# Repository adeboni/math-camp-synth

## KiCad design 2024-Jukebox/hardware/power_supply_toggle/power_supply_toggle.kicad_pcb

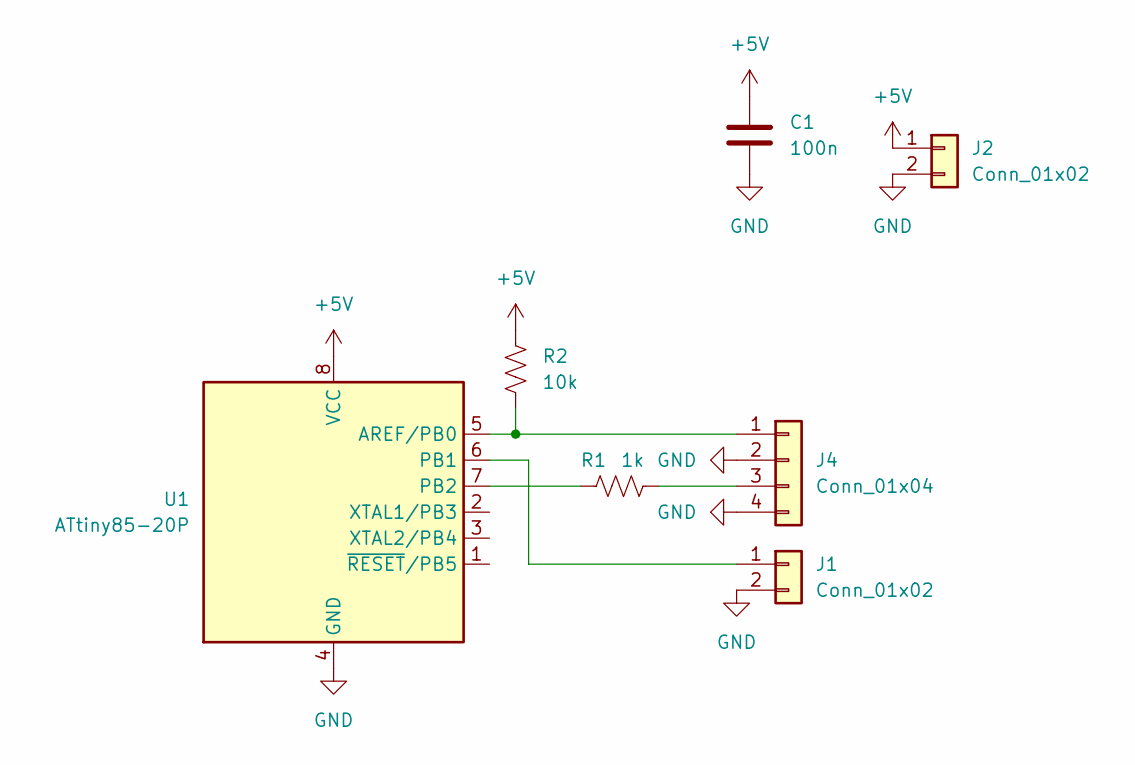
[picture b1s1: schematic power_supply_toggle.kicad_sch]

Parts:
C1: 100n; C_0603_1608Metric
J1, J2: Conn_01x02; PinHeader_1x02_P2.54mm_Vertical
J4: Conn_01x04; JST_XH_B4B-XH-A_1x04_P2.50mm_Vertical
R1: 1k; R_0603_1608Metric
R2: 10k; R_0603_1608Metric
U1: ATtiny85-20P; DIP-8_W7.62mm

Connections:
+5V: C1.1, J2.1, R2.1, U1.8 (VCC)
GND: C1.2, J1.2, J2.2, J4.2, J4.4, U1.4 (GND)
unnamed: J1.1, U1.6 (PB1)
unnamed: J4.1, R2.2, U1.5 (AREF/PB0)
unnamed: J4.3, R1.2
unnamed: R1.1, U1.7 (PB2)

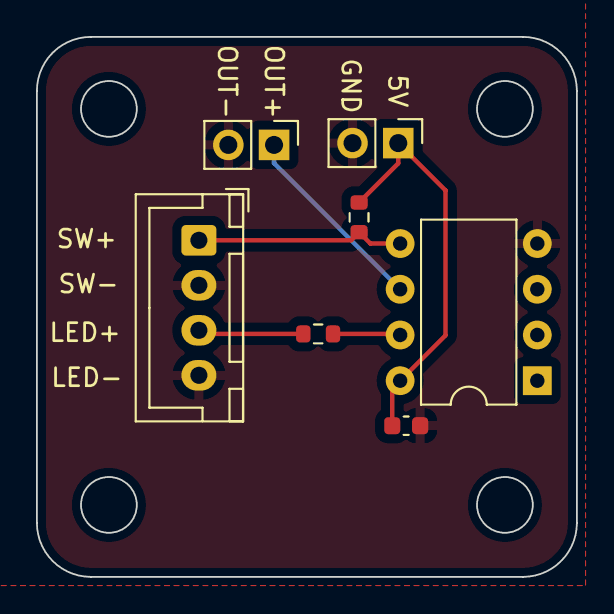
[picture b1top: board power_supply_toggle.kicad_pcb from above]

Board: 2 copper layers, 30.0 x 30.0 mm, 7 parts (0 on the bottom side), 6 nets.

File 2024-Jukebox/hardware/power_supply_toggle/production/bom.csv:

Designator,Footprint,Quantity,Value,LCSC Part #
C1,0603,1,100n,
"J1, J2",PinHeader_1x02_P2.54mm_Vertical,2,Conn_01x02,
J4,JST_XH_B4B-XH-A_1x04_P2.50mm_Vertical,1,Conn_01x04,
R1,0603,1,1k,
R2,0603,1,10k,
U1,DIP-8_W7.62mm,1,ATtiny85-20P,

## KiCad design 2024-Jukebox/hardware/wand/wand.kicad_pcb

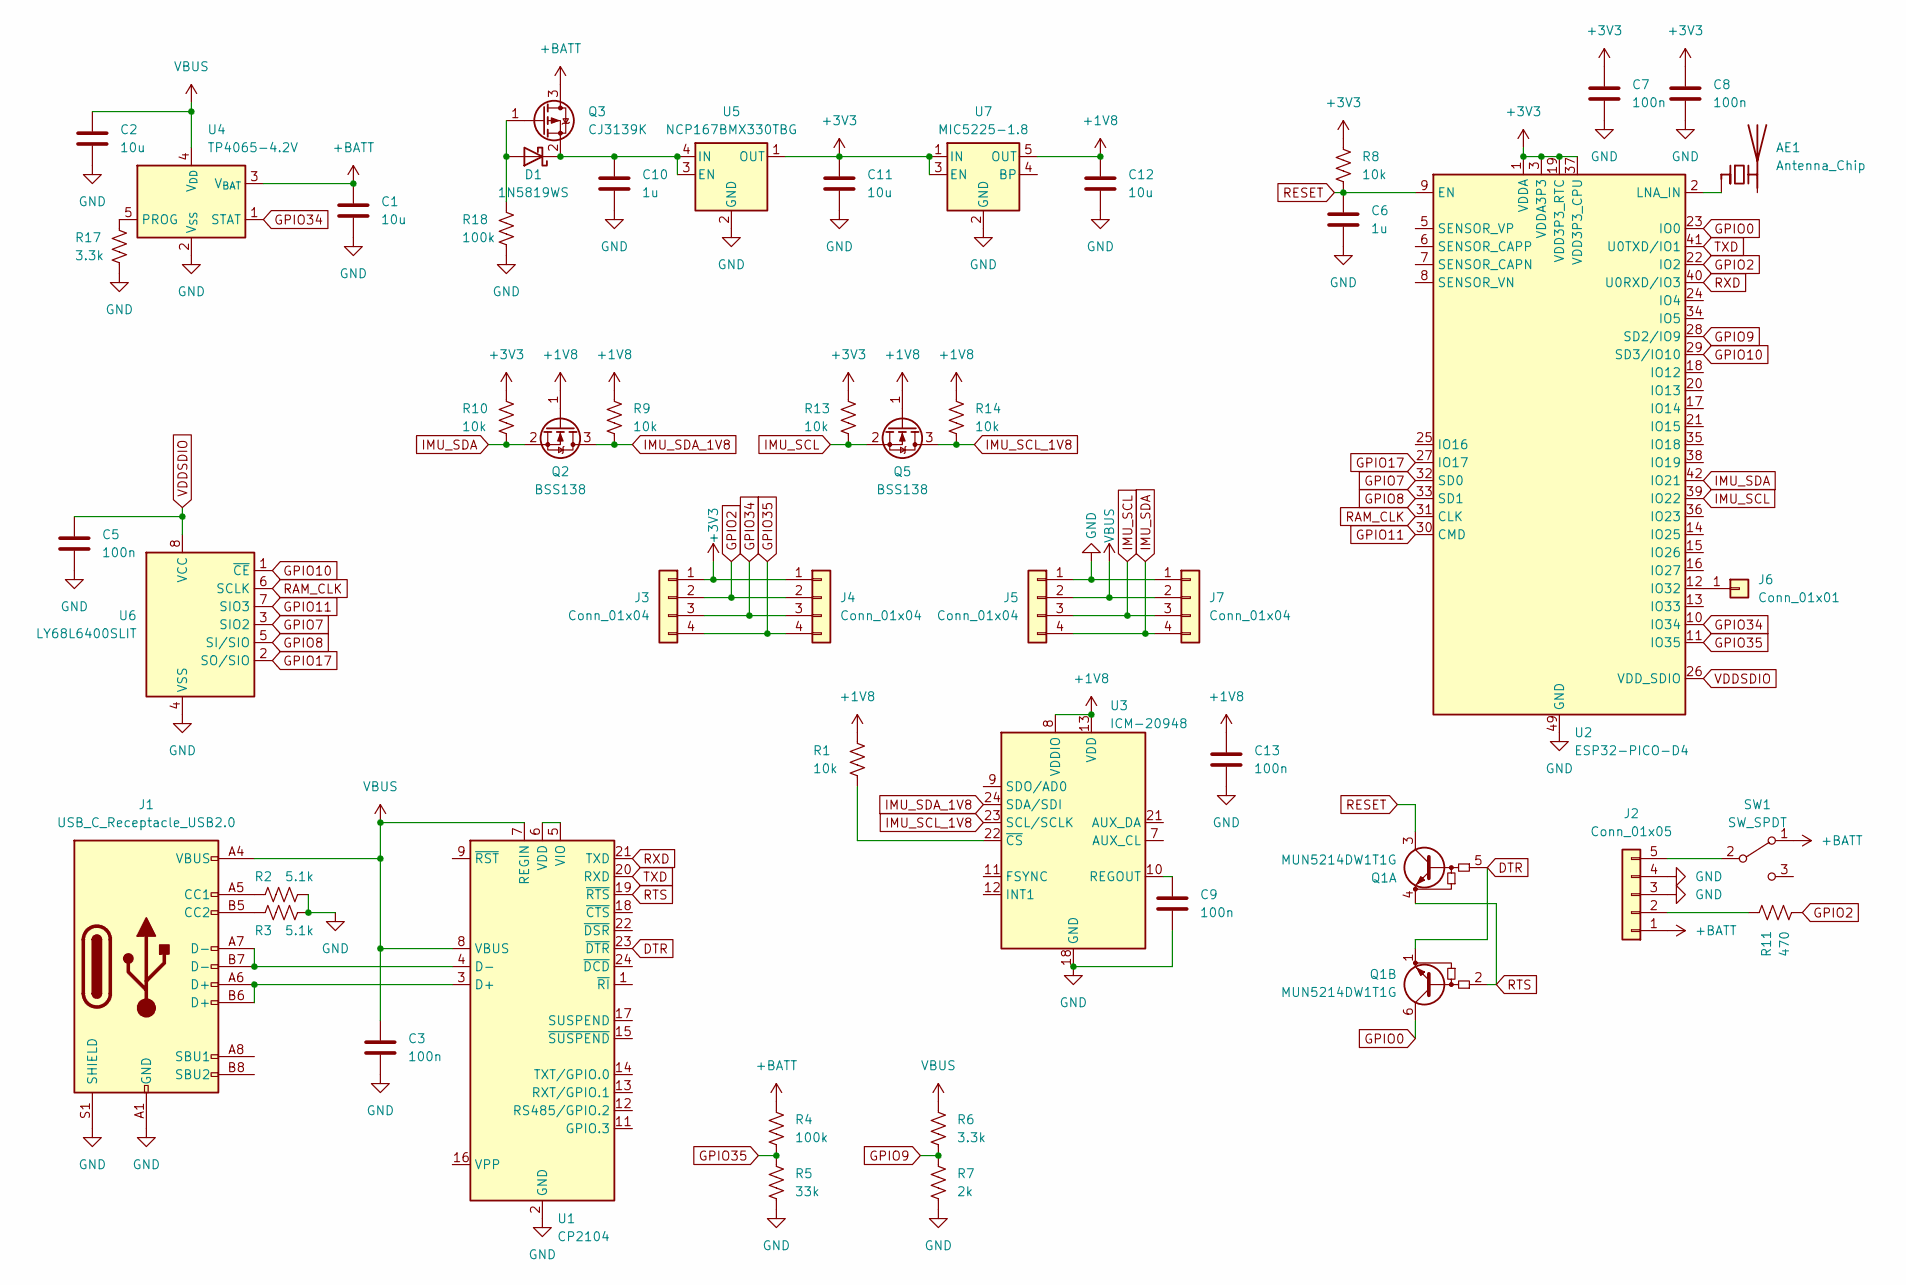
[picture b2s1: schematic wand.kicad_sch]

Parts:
AE1: Antenna_Chip; C_1206_3216Metric
C1, C2, C11, C12: 10u; C_0402_1005Metric
C3, C5, C7, C8, C9, C13: 100n; C_0402_1005Metric
C6, C10: 1u; C_0402_1005Metric
D1: 1N5819WS; D_SOD-323
J1: USB_C_Receptacle_USB2.0; USB_C_Receptacle_Palconn_UTC16-G
J2: Conn_01x05; PinHeader_1x05_P2.54mm_Vertical
J3, J4, J5, J7: Conn_01x04; PinHeader_1x04_P2.54mm_Vertical
J6: Conn_01x01; SolderWire-0.25sqmm_1x01_D0.65mm_OD1.7mm
Q1: MUN5214DW1T1G; SOT-363_SC-70-6
Q2, Q5: BSS138; SOT-23
Q3: CJ3139K; SOT-723
R1, R8, R9, R10, R13, R14: 10k; R_0402_1005Metric
R2, R3: 5.1k; R_0402_1005Metric
R4, R18: 100k; R_0402_1005Metric
R5: 33k; R_0402_1005Metric
R6, R17: 3.3k; R_0402_1005Metric
R7: 2k; R_0402_1005Metric
R11: 470; R_0402_1005Metric
SW1: SW_SPDT; SW_CuK_OS102011MA1QN1_SPDT_Angled
U1: CP2104; QFN-24-1EP_4x4mm_P0.5mm_EP2.6x2.6mm
U2: ESP32-PICO-D4; QFN-48-1EP_7x7mm_P0.5mm_EP5.3x5.3mm
U3: ICM-20948; InvenSense_QFN-24_3x3mm_P0.4mm
U4: TP4065-4.2V; SOT-23-5
U5: NCP167BMX330TBG; OnSemi_XDFN4-1EP_1.0x1.0mm_EP0.52x0.52mm
U6: LY68L6400SLIT; SOIC-8_3.9x4.9mm_P1.27mm
U7: MIC5225-1.8; SOT-23-5

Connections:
+1V8: C12.1, C13.1, Q2.1 (G), Q5.1 (G), R1.1, R9.1, R14.1, U3.8 (VDDIO), U3.13 (VDD), U7.5 (OUT)
+3V3: C7.1, C8.1, C11.1, J3.1, J4.1, R8.1, R10.1, R13.1, U2.1 (VDDA), U2.3 (VDDA3P3), U2.4 (VDDA3P3), U2.19 (VDD3P3_RTC), U2.37 (VDD3P3_CPU), U2.43 (VDDA), U2.46 (VDDA), U5.1 (OUT), U7.1 (IN), U7.3 (EN)
+BATT: C1.1, J2.1, Q3.3 (D), R4.1, SW1.1 (A), U4.3 (V_{BAT})
DTR: Q1.1 (E2), Q1.5 (B1), U1.23 (~DTR)
GND: C1.2, C2.2, C3.2, C5.2, C6.2, C7.2, C8.2, C9.2, C10.2, C11.2, C12.2, C13.2, J1.A1 (GND), J1.A12 (GND), J1.B1 (GND), J1.B12 (GND), J1.S1 (SHIELD), J2.3, J2.4, J5.1, J7.1, R2.2, R3.2, R5.2, R7.2, R17.1, R18.1, U1.2 (GND), U1.25 (GND), U2.49 (GND), U3.18 (GND), U3.20 (GND), U4.2 (V_{SS}), U5.2 (GND), U6.4 (VSS), U7.2 (GND)
GPIO0: Q1.6 (C2), U2.23 (IO0)
GPIO2: J3.2, J4.2, R11.2, U2.22 (IO2)
GPIO7: U2.32 (SD0), U6.3 (SIO2)
GPIO8: U2.33 (SD1), U6.5 (SI/SIO)
GPIO9: R6.2, R7.1, U2.28 (SD2/IO9)
GPIO10: U2.29 (SD3/IO10), U6.1 (~CE)
GPIO11: U2.30 (CMD), U6.7 (SIO3)
GPIO17: U2.27 (IO17), U6.2 (SO/SIO)
GPIO34: J3.3, J4.3, U2.10 (IO34), U4.1 (STAT)
GPIO35: J3.4, J4.4, R4.2, R5.1, U2.11 (IO35)
IMU_SCL: J5.3, J7.3, Q5.2 (S), R13.2, U2.39 (IO22)
IMU_SCL_1V8: Q5.3 (D), R14.2, U3.23 (SCL/SCLK)
IMU_SDA: J5.4, J7.4, Q2.2 (S), R10.2, U2.42 (IO21)
IMU_SDA_1V8: Q2.3 (D), R9.2, U3.24 (SDA/SDI)
unnamed: AE1.1 (FEED), U2.2 (LNA_IN)
unnamed: D1.2 (A), Q3.1 (G), R18.2
unnamed: C10.1, D1.1 (K), Q3.2 (S), U5.3 (EN), U5.4 (IN)
unnamed: J1.A5 (CC1), R2.1
unnamed: J1.B5 (CC2), R3.1
unnamed: J2.2, R11.1
unnamed: J2.5, SW1.2 (B)
unnamed: J6.1, U2.12 (IO32)
unnamed: J1.A6 (D+), J1.B6 (D+), U1.3 (D+)
unnamed: J1.A7 (D-), J1.B7 (D-), U1.4 (D-)
unnamed: U1.5 (VIO), U1.6 (VDD)
unnamed: C9.1, U3.10 (REGOUT)
unnamed: R1.2, U3.22 (~CS)
unnamed: R17.2, U4.5 (PROG)
RAM_CLK: U2.31 (CLK), U6.6 (SCLK)
RESET: C6.1, Q1.3 (C1), R8.2, U2.9 (EN)
RTS: Q1.2 (B2), Q1.4 (E1), U1.19 (~RTS)
RXD: U1.21 (TXD), U2.40 (U0RXD/IO3)
TXD: U1.20 (RXD), U2.41 (U0TXD/IO1)
VBUS: C2.1, C3.1, J1.A4 (VBUS), J1.A9 (VBUS), J1.B4 (VBUS), J1.B9 (VBUS), J5.2, J7.2, R6.1, U1.7 (REGIN), U1.8 (VBUS), U4.4 (V_{DD})
VDDSDIO: C5.1, U2.26 (VDD_SDIO), U6.8 (VCC)

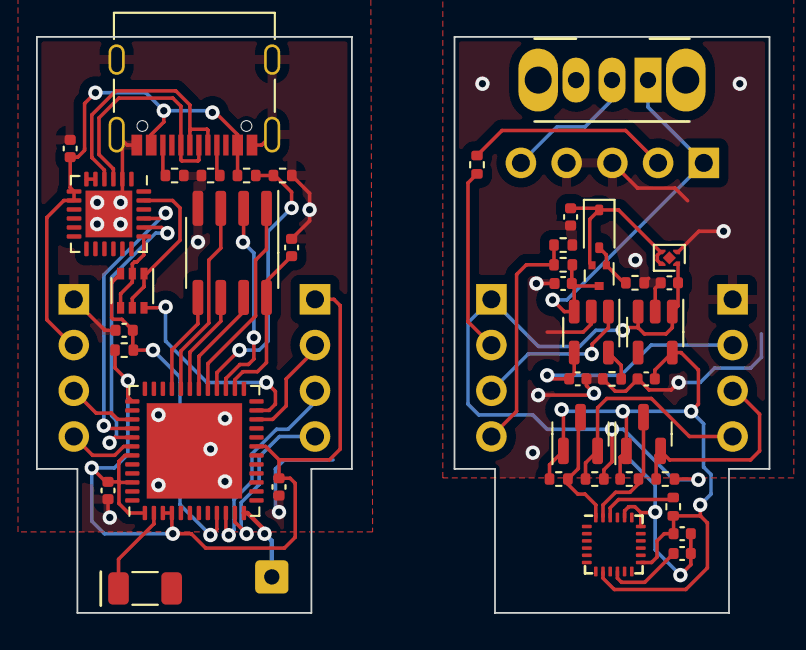
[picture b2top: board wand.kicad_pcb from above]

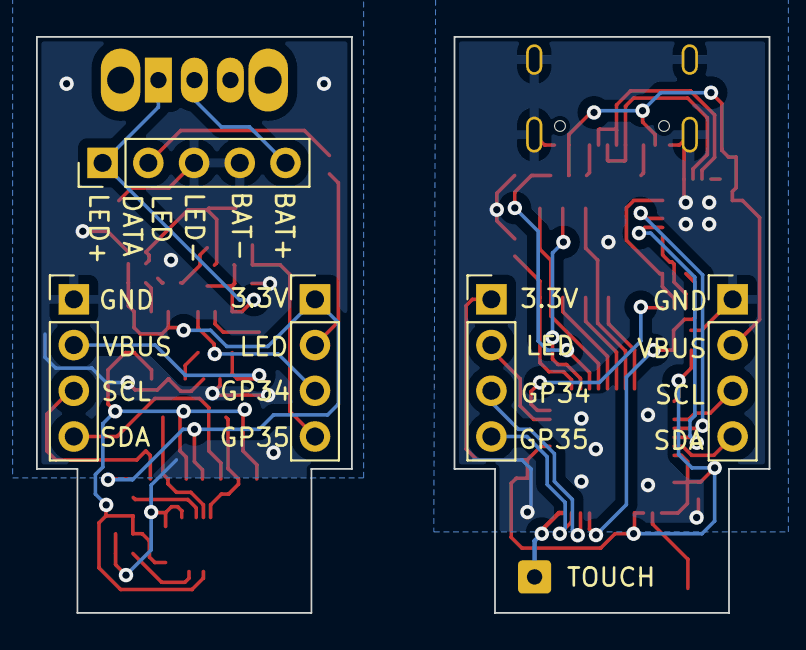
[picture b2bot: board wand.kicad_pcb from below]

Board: 2 copper layers, 40.7 x 32.0 mm, 48 parts (5 on the bottom side), 40 nets.

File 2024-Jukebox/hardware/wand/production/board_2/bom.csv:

Designator,Footprint,Quantity,Value,LCSC Part #
"C1, C11, C12, C2",402,4,10u,C15525
C10,402,1,1u,C52923
"C13, C9",402,2,100n,C307331
D1,D_SOD-323,1,1N5819WS,C191023
"Q2, Q5",SOT-23,2,BSS138,C7420339
Q3,SOT-723,1,CJ3139K,C70022
"R1, R10, R13, R14, R9",402,5,10k,C25744
R11,402,1,470,C25117
R17,402,1,3.3k,C25890
"R18, R4",402,2,100k,C25741
R5,402,1,33k,C25779
U3,InvenSense_QFN-24_3x3mm_P0.4mm,1,ICM-20948,C726001
U4,SOT-23-5,1,TP4065-4.2V,C113540
U5,OnSemi_XDFN4-1EP_1.0x1.0mm_EP0.52x0.52mm,1,NCP167BMX330TBG,C892227
U7,SOT-23-5,1,MIC5225-1.8,C625861

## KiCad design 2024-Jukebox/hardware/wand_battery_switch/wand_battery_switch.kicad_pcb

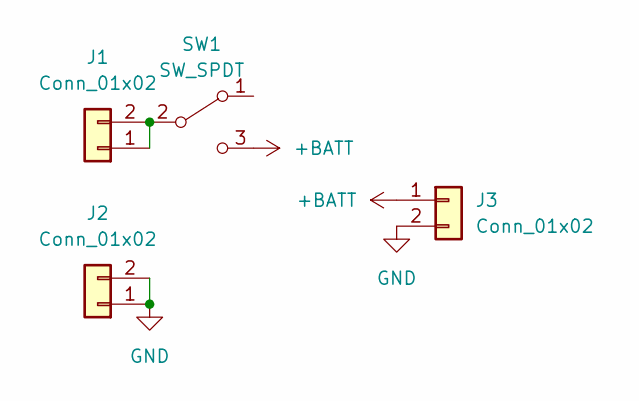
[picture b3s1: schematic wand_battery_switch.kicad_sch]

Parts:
J1, J2, J3: Conn_01x02; PinHeader_1x02_P2.54mm_Vertical
SW1: SW_SPDT; SW_CuK_OS102011MA1QN1_SPDT_Angled

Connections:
+BATT: J3.1, SW1.3 (C)
GND: J2.1, J2.2, J3.2
unnamed: J1.1, J1.2, SW1.2 (B)

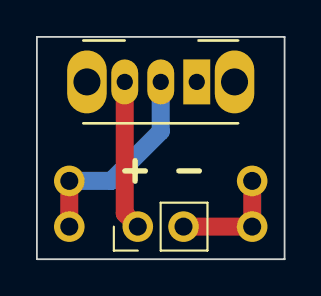
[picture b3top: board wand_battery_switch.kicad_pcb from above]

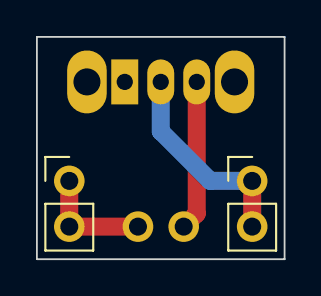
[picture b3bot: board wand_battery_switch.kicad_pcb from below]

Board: 2 copper layers, 13.8 x 12.3 mm, 4 parts (2 on the bottom side), 3 nets.

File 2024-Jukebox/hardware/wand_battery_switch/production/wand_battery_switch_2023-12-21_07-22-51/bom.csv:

Designator,Footprint,Quantity,Value,LCSC Part #
"J1, J2, J3",PinHeader_1x02_P2.54mm_Vertical,3,Conn_01x02,
SW1,SW_CuK_OS102011MA1QN1_SPDT_Angled,1,SW_SPDT,

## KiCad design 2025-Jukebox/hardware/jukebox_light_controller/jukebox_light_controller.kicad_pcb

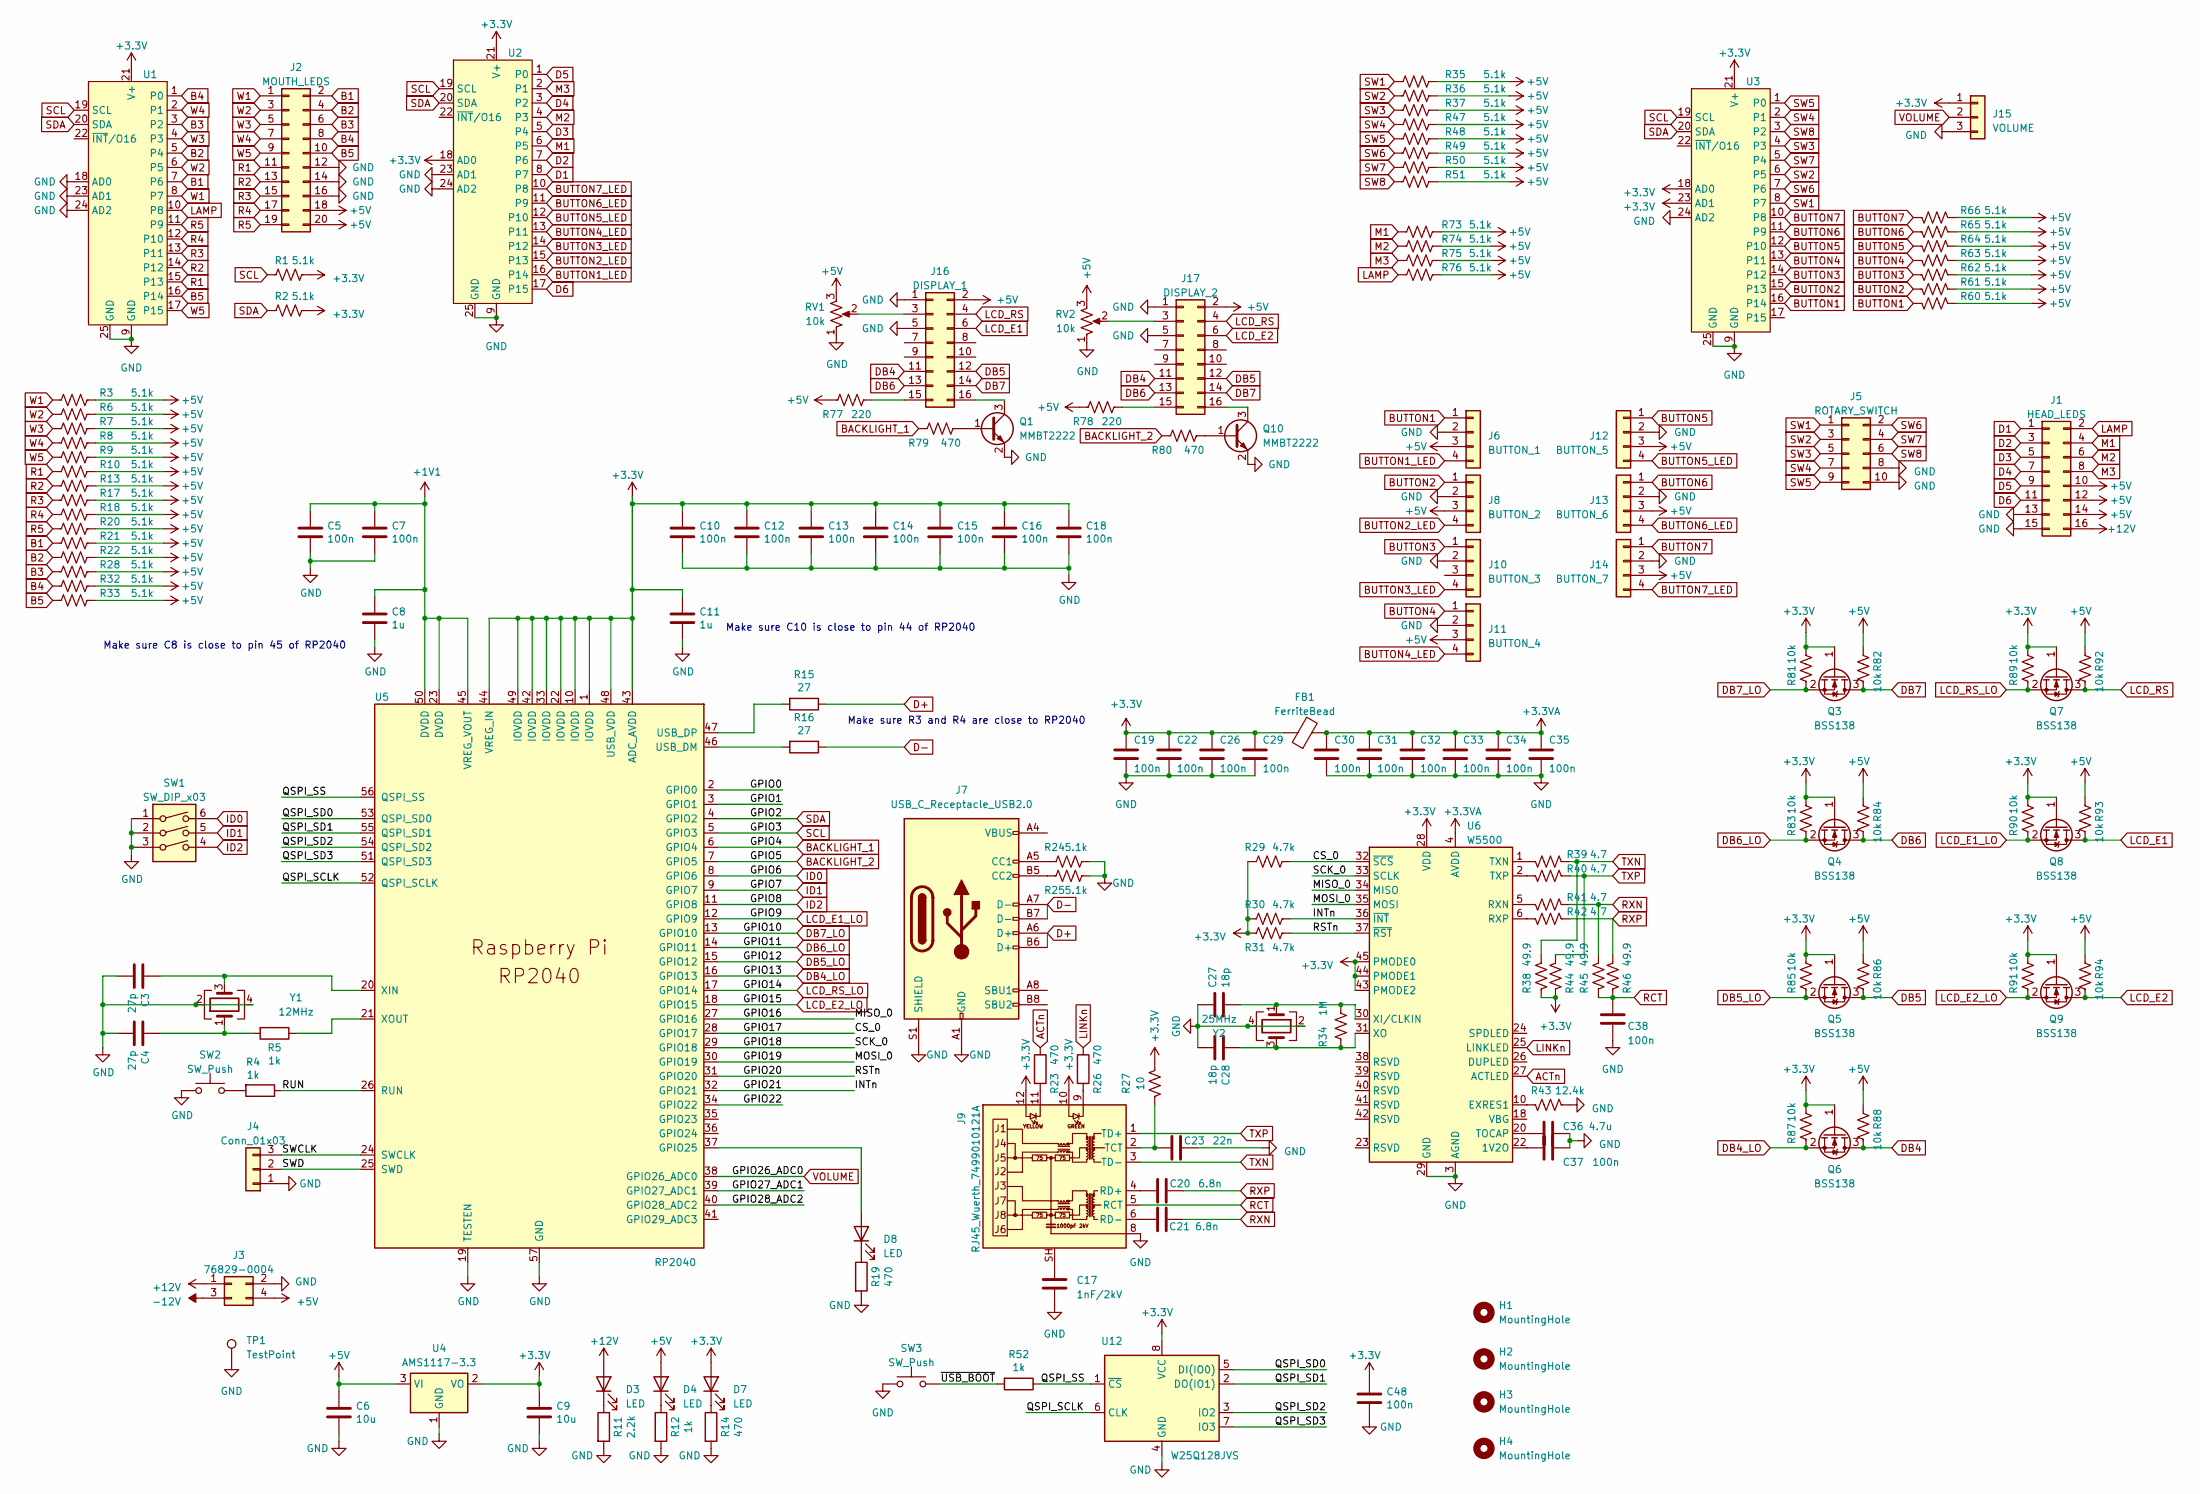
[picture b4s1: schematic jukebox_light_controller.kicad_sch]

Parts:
C3, C4: 27p; C_0603_1608Metric
C5, C7, C10, C12, C13, C14, C15, C16, C18, C19, C22, C26, C29, C30, C31, C32, C33, C34, C35, C37, C38, C48: 100n; C_0603_1608Metric
C6, C9: 10u; C_0603_1608Metric
C8, C11: 1u; C_0603_1608Metric
C17: 1nF/2kV; C_1206_3216Metric
C20, C21: 6.8n; C_0603_1608Metric
C23: 22n; C_0603_1608Metric
C27, C28: 18p; C_0603_1608Metric
C36: 4.7u; C_0603_1608Metric
D3, D4, D7, D8: LED; LED_0603_1608Metric
FB1: FerriteBead; L_0603_1608Metric
H1, H2, H3, H4: MountingHole; MountingHole_3.2mm_M3
J1: HEAD_LEDS; IDC-Header_2x08_P2.54mm_Vertical
J2: MOUTH_LEDS; IDC-Header_2x10_P2.54mm_Vertical
J3: 76829-0004; Molex_Mega-Fit_76829-0004_2x02_P5.70mm_Vertical
J4: Conn_01x03; PinHeader_1x03_P2.54mm_Vertical
J5: ROTARY_SWITCH; IDC-Header_2x05_P2.54mm_Vertical
J6: BUTTON_1; JST_XH_B4B-XH-A_1x04_P2.50mm_Vertical
J7: USB_C_Receptacle_USB2.0; USB_C_Receptacle_Palconn_UTC16-G
J8: BUTTON_2; JST_XH_B4B-XH-A_1x04_P2.50mm_Vertical
J9: RJ45_Wuerth_7499010121A; RJ45_Wuerth_7499010121A_Horizontal
J10: BUTTON_3; JST_XH_B4B-XH-A_1x04_P2.50mm_Vertical
J11: BUTTON_4; JST_XH_B4B-XH-A_1x04_P2.50mm_Vertical
J12: BUTTON_5; JST_XH_B4B-XH-A_1x04_P2.50mm_Vertical
J13: BUTTON_6; JST_XH_B4B-XH-A_1x04_P2.50mm_Vertical
J14: BUTTON_7; JST_XH_B4B-XH-A_1x04_P2.50mm_Vertical
J15: VOLUME; JST_XH_B3B-XH-A_1x03_P2.50mm_Vertical
J16: DISPLAY_1; IDC-Header_2x08_P2.54mm_Vertical
J17: DISPLAY_2; IDC-Header_2x08_P2.54mm_Vertical
Q1, Q10: MMBT2222; SOT-23
Q3, Q4, Q5, Q6, Q7, Q8, Q9: BSS138; SOT-23
R1, R2, R3, R6, R7, R8, R9, R10, R13, R17, R18, R20, R21, R22, R24, R25, R28, R32, R33, R35, R36, R37, R47, R48, R49, R50, R51, R60, R61, R62, R63, R64, R65, R66, R73, R74, R75, R76: 5.1k; R_0603_1608Metric
R4, R5, R12, R52: 1k; R_0603_1608Metric
R11: 2.2k; R_0603_1608Metric
R14, R19, R23, R26, R79, R80: 470; R_0603_1608Metric
R15, R16: 27; R_0603_1608Metric
R27: 10; R_0603_1608Metric
R29, R30, R31: 4.7k; R_0603_1608Metric
R34: 1M; R_0603_1608Metric
R38, R44, R45, R46: 49.9; R_0603_1608Metric
R39, R40, R41, R42: 4.7; R_0603_1608Metric
R43: 12.4k; R_0603_1608Metric
R77, R78: 220; R_0603_1608Metric
R81, R82, R83, R84, R85, R86, R87, R88, R89, R90, R91, R92, R93, R94: 10k; R_0603_1608Metric
RV1, RV2: 10k; Potentiometer_Bourns_3386P_Vertical
SW1: SW_DIP_x03; SW_DIP_SPSTx03_Slide_9.78x9.8mm_W7.62mm_P2.54mm
SW2, SW3: SW_Push; SW_SPST_TL3342
TP1: TestPoint; TestPoint_Loop_D2.60mm_Drill1.4mm_Beaded
U1, U2, U3: TQFN-24-1EP_4x4mm_P0.5mm_EP2.6x2.6mm_ThermalVias
U4: AMS1117-3.3; SOT-223-3_TabPin2
U5: RP2040; QFN-56-1EP_7x7mm_P0.4mm_EP3.2x3.2mm
U6: W5500; LQFP-48_7x7mm_P0.5mm
U12: W25Q128JVS; SOIC-8_5.23x5.23mm_P1.27mm
Y1: 12MHz; Crystal_SMD_3225-4Pin_3.2x2.5mm
Y2: 25MHz; Crystal_SMD_3225-4Pin_3.2x2.5mm

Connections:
+1V1: C5.1, C7.1, C8.1, U5.23 (DVDD), U5.45 (VREG_VOUT), U5.50 (DVDD)
+3.3V: C9.1, C10.1, C11.1, C12.1, C13.1, C14.1, C15.1, C16.1, C18.1, C19.1, C22.1, C26.1, C29.1, C48.1, D7.2 (A), FB1.1, J9.10, J9.12, J15.1, Q3.1 (G), Q4.1 (G), Q5.1 (G), Q6.1 (G), Q7.1 (G), Q8.1 (G), Q9.1 (G), R1.2, R2.2, R27.2, R29.1, R30.1, R31.1, R38.2, R44.2, R81.2, R83.2, R85.2, R87.2, R89.2, R90.2, R91.2, U1.21 (V+), U2.18 (AD0), U2.21 (V+), U3.18 (AD0), U3.21 (V+), U3.23 (AD1), U4.2 (VO), U5.1 (IOVDD), U5.10 (IOVDD), U5.22 (IOVDD), U5.33 (IOVDD), U5.42 (IOVDD), U5.43 (ADC_AVDD), U5.44 (VREG_IN), U5.48 (USB_VDD), U5.49 (IOVDD), U6.28 (VDD), U6.43 (PMODE2), U6.44 (PMODE1), U6.45 (PMODE0), U12.8 (VCC)
+3.3VA: C30.1, C31.1, C32.1, C33.1, C34.1, C35.1, FB1.2, U6.4 (AVDD), U6.8 (AVDD), U6.11 (AVDD), U6.15 (AVDD), U6.17 (AVDD), U6.21 (AVDD)
+5V: C6.1, D4.2 (A), J1.10, J1.12, J1.14, J2.18, J2.20, J3.4, J6.3, J8.3, J11.3, J12.3, J13.3, J14.3, J16.2, J17.2, R3.2, R6.2, R7.2, R8.2, R9.2, R10.2, R13.2, R17.2, R18.2, R20.2, R21.2, R22.2, R28.2, R32.2, R33.2, R35.2, R36.2, R37.2, R47.2, R48.2, R49.2, R50.2, R51.2, R60.2, R61.2, R62.2, R63.2, R64.2, R65.2, R66.2, R73.2, R74.2, R75.2, R76.2, R77.1, R78.1, R82.1, R84.1, R86.1, R88.1, R92.1, R93.1, R94.1, RV1.3, RV2.3, U4.3 (VI)
+12V: D3.2 (A), J1.16, J3.1
-12V: J3.3
/CS_0: R29.2, U5.28 (GPIO17), U6.32 (~SCS)
/GPIO0: U5.2 (GPIO0)
/GPIO1: U5.3 (GPIO1)
/GPIO16: U5.27 (GPIO16), U6.34 (MISO)
/GPIO18: U5.29 (GPIO18), U6.33 (SCLK)
/GPIO19: U5.30 (GPIO19), U6.35 (MOSI)
/GPIO20: R31.2, U5.31 (GPIO20), U6.37 (~RST)
/GPIO21: R30.2, U5.32 (GPIO21), U6.36 (~INT)
/GPIO22: U5.34 (GPIO22)
/GPIO27_ADC1: U5.39 (GPIO27_ADC1)
/GPIO28_ADC2: U5.40 (GPIO28_ADC2)
/QSPI_SCLK: U5.52 (QSPI_SCLK), U12.6 (CLK)
/QSPI_SD0: U5.53 (QSPI_SD0), U12.5 (DI(IO0))
/QSPI_SD1: U5.55 (QSPI_SD1), U12.2 (DO(IO1))
/QSPI_SD2: U5.54 (QSPI_SD2), U12.3 (IO2)
/QSPI_SD3: U5.51 (QSPI_SD3), U12.7 (IO3)
/QSPI_SS: R52.1, U5.56 (QSPI_SS), U12.1 (~CS)
/RUN: R4.1, U5.26 (RUN)
/SWCLK: J4.3, U5.24 (SWCLK)
/SWD: J4.2, U5.25 (SWD)
/~USB_BOOT: R52.2, SW3.2
ACTn: R23.1, U6.27 (ACTLED)
B1: J2.2, R21.1, U1.7 (P6)
B2: J2.4, R22.1, U1.5 (P4)
B3: J2.6, R28.1, U1.3 (P2)
B4: J2.8, R32.1, U1.1 (P0)
B5: J2.10, R33.1, U1.16 (P14)
BACKLIGHT_1: R79.1, U5.6 (GPIO4)
BACKLIGHT_2: R80.1, U5.7 (GPIO5)
BUTTON1: J6.1, R60.1, U3.16 (P14)
BUTTON1_LED: J6.4, U2.16 (P14)
BUTTON2: J8.1, R61.1, U3.15 (P13)
BUTTON2_LED: J8.4, U2.15 (P13)
BUTTON3: J10.1, R62.1, U3.14 (P12)
BUTTON3_LED: J10.4, U2.14 (P12)
BUTTON4: J11.1, R63.1, U3.13 (P11)
BUTTON4_LED: J11.4, U2.13 (P11)
BUTTON5: J12.1, R64.1, U3.12 (P10)
BUTTON5_LED: J12.4, U2.12 (P10)
BUTTON6: J13.1, R65.1, U3.11 (P9)
BUTTON6_LED: J13.4, U2.11 (P9)
BUTTON7: J14.1, R66.1, U3.10 (P8)
BUTTON7_LED: J14.4, U2.10 (P8)
D1: J1.1, U2.8 (P7)
D2: J1.3, U2.7 (P6)
D3: J1.5, U2.5 (P4)
D4: J1.7, U2.3 (P2)
D5: J1.9, U2.1 (P0)
D6: J1.11, U2.17 (P15)
D+: J7.A6 (D+), J7.B6 (D+), R15.1
D-: J7.A7 (D-), J7.B7 (D-), R16.1
DB4: J16.11, J17.11, Q6.3 (D), R88.2
DB4_LO: Q6.2 (S), R87.1, U5.16 (GPIO13)
DB5: J16.12, J17.12, Q5.3 (D), R86.2
DB5_LO: Q5.2 (S), R85.1, U5.15 (GPIO12)
DB6: J16.13, J17.13, Q4.3 (D), R84.2
DB6_LO: Q4.2 (S), R83.1, U5.14 (GPIO11)
DB7: J16.14, J17.14, Q3.3 (D), R82.2
DB7_LO: Q3.2 (S), R81.1, U5.13 (GPIO10)
GND: C3.2, C4.2, C5.2, C6.2, C7.2, C8.2, C9.2, C10.2, C11.2, C12.2, C13.2, C14.2, C15.2, C16.2, C17.2, C18.2, C19.2, C22.2, C23.1, C26.2, C27.1, C28.2, C29.2, C30.2, C31.2, C32.2, C33.2, C34.2, C35.2, C36.2, C37.2, C38.1, C48.2, J1.13, J1.15, J2.12, J2.14, J2.16, J3.2, J4.1, J5.8, J5.10, J6.2, J7.A1 (GND), J7.A12 (GND), J7.B1 (GND), J7.B12 (GND), J7.S1 (SHIELD), J8.2, J9.8, J10.2, J11.2, J12.2, J13.2, J14.2, J15.3, J16.1, J16.5, J17.1, J17.5, Q1.2 (E), Q10.2 (E), R11.2, R12.2, R14.2, R19.2, R24.1, R25.1, R43.1, RV1.1, RV2.1, SW1.1, SW1.2, SW1.3, SW2.1, SW3.1, TP1.1, U1.9 (GND), U1.18 (AD0), U1.23 (AD1), U1.24 (AD2), U1.25 (GND), U2.9 (GND), U2.23 (AD1), U2.24 (AD2), U2.25 (GND), U3.9 (GND), U3.24 (AD2), U3.25 (GND), U4.1 (GND), U5.19 (TESTEN), U5.57 (GND), U6.3 (AGND), U6.9 (AGND), U6.14 (AGND), U6.16 (AGND), U6.19 (AGND), U6.29 (GND), U6.48 (AGND), U12.4 (GND), Y1.2, Y1.4, Y2.2, Y2.4
ID0: SW1.6, U5.8 (GPIO6)
ID1: SW1.5, U5.9 (GPIO7)
ID2: SW1.4, U5.11 (GPIO8)
LAMP: J1.2, R76.1, U1.10 (P8)
LCD_E1: J16.6, Q8.3 (D), R93.2
LCD_E1_LO: Q8.2 (S), R90.1, U5.12 (GPIO9)
LCD_E2: J17.6, Q9.3 (D), R94.2
LCD_E2_LO: Q9.2 (S), R91.1, U5.18 (GPIO15)
LCD_RS: J16.4, J17.4, Q7.3 (D), R92.2
LCD_RS_LO: Q7.2 (S), R89.1, U5.17 (GPIO14)
LINKn: R26.1, U6.25 (LINKLED)
M1: J1.4, R73.1, U2.6 (P5)
M2: J1.6, R74.1, U2.4 (P3)
M3: J1.8, R75.1, U2.2 (P1)
unnamed: C4.1, R5.2, Y1.1
unnamed: C17.1, J9.SH
unnamed: D3.1 (K), R11.1
unnamed: D4.1 (K), R12.1
unnamed: D7.1 (K), R14.1
unnamed: D8.2 (A), U5.37 (GPIO25)
unnamed: D8.1 (K), R19.1
unnamed: J7.A5 (CC1), R24.2
unnamed: J7.B5 (CC2), R25.2
unnamed: J7.A4 (VBUS), J7.A9 (VBUS), J7.B4 (VBUS), J7.B9 (VBUS)
unnamed: J9.9, R26.2
unnamed: J9.11, R23.2
unnamed: C20.2, J9.4 (RD+)
unnamed: C21.1, J9.6 (RD-)
unnamed: C23.2, J9.2 (TCT), R27.1
unnamed: J16.3, RV1.2
unnamed: J16.15, R77.2
unnamed: J16.16, Q1.3 (C)
unnamed: J17.3, RV2.2
unnamed: J17.15, R78.2
unnamed: J17.16, Q10.3 (C)
unnamed: Q1.1 (B), R79.2
unnamed: Q10.1 (B), R80.2
unnamed: R4.2, SW2.2
unnamed: R16.2, U5.46 (USB_DM)
unnamed: R15.2, U5.47 (USB_DP)
unnamed: C3.1, U5.20 (XIN), Y1.3
unnamed: R5.1, U5.21 (XOUT)
unnamed: C37.1, U6.22 (1V2O)
unnamed: R43.2, U6.10 (EXRES1)
unnamed: R41.1, U6.5 (RXN)
unnamed: R42.2, U6.6 (RXP)
unnamed: C36.1, U6.20 (TOCAP)
unnamed: R39.1, U6.1 (TXN)
unnamed: R40.2, U6.2 (TXP)
unnamed: C27.2, R34.2, U6.30 (XI/CLKIN), Y2.1
unnamed: C28.1, R34.1, U6.31 (XO), Y2.3
R1: J2.11, R10.1, U1.15 (P13)
R2: J2.13, R13.1, U1.14 (P12)
R3: J2.15, R17.1, U1.13 (P11)
R4: J2.17, R18.1, U1.12 (P10)
R5: J2.19, R20.1, U1.11 (P9)
RCT: C38.2, J9.5 (RCT), R45.2, R46.2
RXN: C21.2, R41.2, R45.1
RXP: C20.1, R42.1, R46.1
SCL: R1.1, U1.19 (SCL), U2.19 (SCL), U3.19 (SCL), U5.5 (GPIO3)
SDA: R2.1, U1.20 (SDA), U2.20 (SDA), U3.20 (SDA), U5.4 (GPIO2)
SW1: J5.1, R35.1, U3.8 (P7)
SW2: J5.3, R36.1, U3.6 (P5)
SW3: J5.5, R37.1, U3.4 (P3)
SW4: J5.7, R47.1, U3.2 (P1)
SW5: J5.9, R48.1, U3.1 (P0)
SW6: J5.2, R49.1, U3.7 (P6)
SW7: J5.4, R50.1, U3.5 (P4)
SW8: J5.6, R51.1, U3.3 (P2)
TXN: J9.3 (TD-), R38.1, R39.2
TXP: J9.1 (TD+), R40.1, R44.1
VOLUME: J15.2, U5.38 (GPIO26_ADC0)
W1: J2.1, R3.1, U1.8 (P7)
W2: J2.3, R6.1, U1.6 (P5)
W3: J2.5, R7.1, U1.4 (P3)
W4: J2.7, R8.1, U1.2 (P1)
W5: J2.9, R9.1, U1.17 (P15)

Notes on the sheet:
Make sure R3 and R4 are close to RP2040
Make sure C10 is close to pin 44 of RP2040
Make sure C8 is close to pin 45 of RP2040

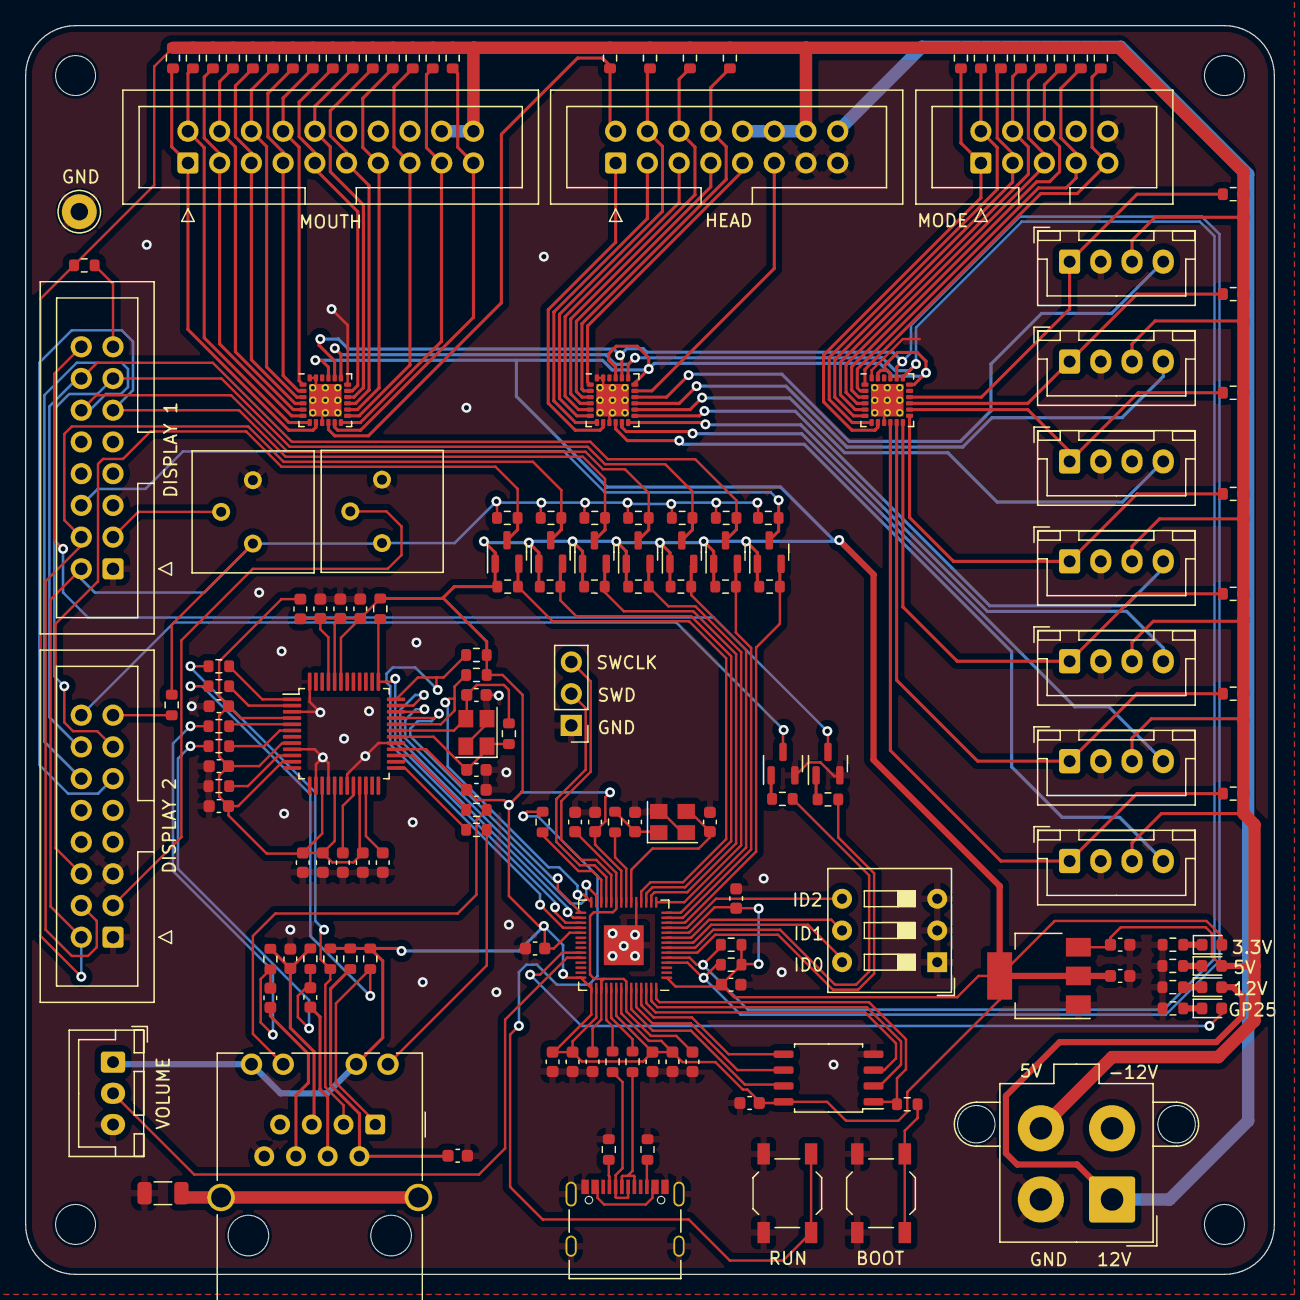
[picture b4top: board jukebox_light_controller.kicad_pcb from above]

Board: 2 copper layers, 100.0 x 100.0 mm, 166 parts (0 on the bottom side), 137 nets.

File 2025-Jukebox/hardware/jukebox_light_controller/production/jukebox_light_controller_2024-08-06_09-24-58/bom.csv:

Designator,Footprint,Quantity,Value,LCSC Part #
"C10, C12, C13, C14, C15, C16, C18, C19, C22, C26, C29, C30, C31, C32, C33, C34, C35, C37, C38, C48, C5, C7",0603,22,100n,C14663
"C11, C8",0603,2,1u,C15849
C17,1206,1,1nF/2kV,C9196
"C20, C21",0603,2,6.8n,C1631
C23,0603,1,22n,C21122
"C27, C28",0603,2,18p,C1647
"C3, C4",0603,2,27p,C107045
C36,0603,1,4.7u,C19666
"C6, C9",0603,2,10u,C96446
"D3, D4, D7, D8",0603,4,LED,C2286
FB1,0603,1,FerriteBead,C1002
J7,USB_C_Receptacle_Palconn_UTC16-G,1,USB_C_Receptacle_USB2.0,C709357
"Q1, Q10",SOT-23,2,MMBT2222,C8512
"Q3, Q4, Q5, Q6, Q7, Q8, Q9",SOT-23,7,BSS138,C7420339
"R1, R10, R13, R17, R18, R2, R20, R21, R22, R24, R25, R28, R3, R32, R33, R35, R36, R37, R47, R48, R49, R50, R51, R6, R60, R61, R62, R63, R64, R65, R66, R7, R73, R74, R75, R76, R8, R9",0603,38,5.1k,C23186
R11,0603,1,2.2k,C4190
"R12, R4, R5, R52",0603,4,1k,C21190
"R14, R19, R23, R26, R79, R80",0603,6,470,C23179
"R15, R16",0603,2,27,C25190
R27,0603,1,10,C22859
"R29, R30, R31",0603,3,4.7k,C23162
R34,0603,1,1M,C22935
"R38, R44, R45, R46",0603,4,49.9,C23185
"R39, R40, R41, R42",0603,4,4.7,C23164
R43,0603,1,12.4k,C22865
"R77, R78",0603,2,220,C22962
"R81, R82, R83, R84, R85, R86, R87, R88, R89, R90, R91, R92, R93, R94",0603,14,10k,C25804
"SW2, SW3",SW_SPST_TL3342,2,SW_Push,C318884
"U1, U2, U3",TQFN-24-1EP_4x4mm_P0.5mm_EP2.6x2.6mm_ThermalVias,3,MAX7313,C2669657
U12,SOIC-8_5.23x5.23mm_P1.27mm,1,W25Q128JVS,C97521
U4,SOT-223-3_TabPin2,1,AMS1117-3.3,C6186
U5,QFN-56-1EP_7x7mm_P0.4mm_EP3.2x3.2mm,1,RP2040,C2040
U6,LQFP-48_7x7mm_P0.5mm,1,W5500,C32843
Y1,Crystal_SMD_3225-4Pin_3.2x2.5mm,1,12MHz,C9002
Y2,Crystal_SMD_3225-4Pin_3.2x2.5mm,1,25MHz,C9006

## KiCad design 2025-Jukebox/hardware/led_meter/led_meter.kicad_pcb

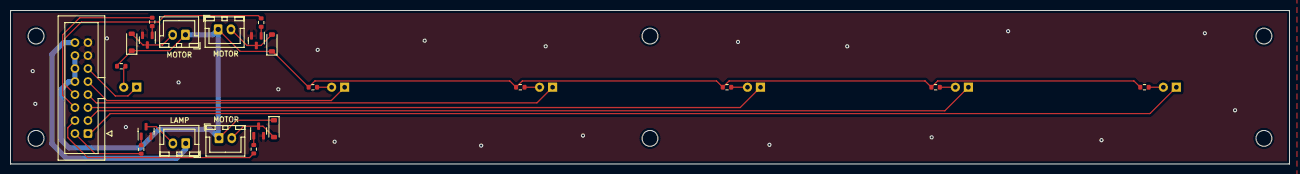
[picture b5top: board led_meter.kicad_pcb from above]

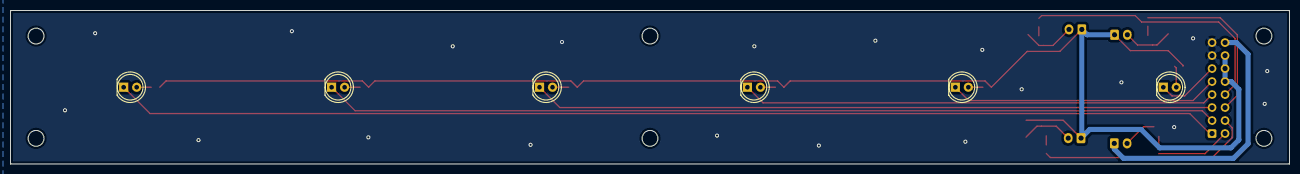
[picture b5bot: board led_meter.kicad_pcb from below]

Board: 2 copper layers, 250.0 x 30.0 mm, 28 parts (6 on the bottom side), 27 nets.

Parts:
D1, D2, D3, D4, D5, D6: LED; LED_D5.0mm_Clear
D7, D8, D9: 1N4148W; D_SOD-123
J1, J2, J3, J4: Conn_01x02; JST_XH_B2B-XH-A_1x02_P2.50mm_Vertical
J5: HEAD_LEDS; IDC-Header_2x08_P2.54mm_Vertical
Q1, Q2, Q3, Q4: 2N7002; SOT-23
R1, R2, R3, R4, R5, R6: 1k; R_0603_1608Metric
R7, R8, R9, R10: 100; R_0603_1608Metric

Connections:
+5V: D7.1 (K), D8.1 (K), D9.1 (K), J1.1, J2.1, J3.1, J5.10, J5.12, J5.14, R1.1, R2.1, R3.1, R4.1, R5.1, R6.1
+12V: J4.1, J5.16
D1: D1.1 (K), J5.1
D2: D2.1 (K), J5.3
D3: D3.1 (K), J5.5
D4: D4.1 (K), J5.7
D5: D5.1 (K), J5.9
D6: D6.1 (K), J5.11
GND: J5.13, J5.15, Q1.2 (S), Q2.2 (S), Q3.2 (S), Q4.2 (S)
LAMP: J5.2, R10.1
M1: J5.4, R7.1
M2: J5.6, R8.1
M3: J5.8, R9.1
unnamed: D1.2 (A), R1.2
unnamed: D2.2 (A), R2.2
unnamed: D3.2 (A), R3.2
unnamed: D4.2 (A), R4.2
unnamed: D5.2 (A), R5.2
unnamed: D6.2 (A), R6.2
unnamed: D7.2 (A), J1.2, Q1.3 (D)
unnamed: D8.2 (A), J2.2, Q2.3 (D)
unnamed: D9.2 (A), J3.2, Q3.3 (D)
unnamed: J4.2, Q4.3 (D)
unnamed: Q1.1 (G), R7.2
unnamed: Q2.1 (G), R8.2
unnamed: Q3.1 (G), R9.2
unnamed: Q4.1 (G), R10.2

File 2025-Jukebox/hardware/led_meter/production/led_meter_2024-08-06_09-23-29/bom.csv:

Designator,Footprint,Quantity,Value,LCSC Part #
"D7, D8, D9",D_SOD-123,3,1N4148W,C81598
"Q1, Q2, Q3, Q4",SOT-23,4,2N7002,C8545
"R1, R2, R3, R4, R5, R6",0603,6,1k,C21190
"R10, R7, R8, R9",0603,4,100,C22775
